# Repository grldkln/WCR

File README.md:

Please note that this repository is used only as a showcase for my final thesis project.
All of the designs are made by myself, with some code dependencies.
This project is not meant to be developed further, but can be used as a reference or as an example.

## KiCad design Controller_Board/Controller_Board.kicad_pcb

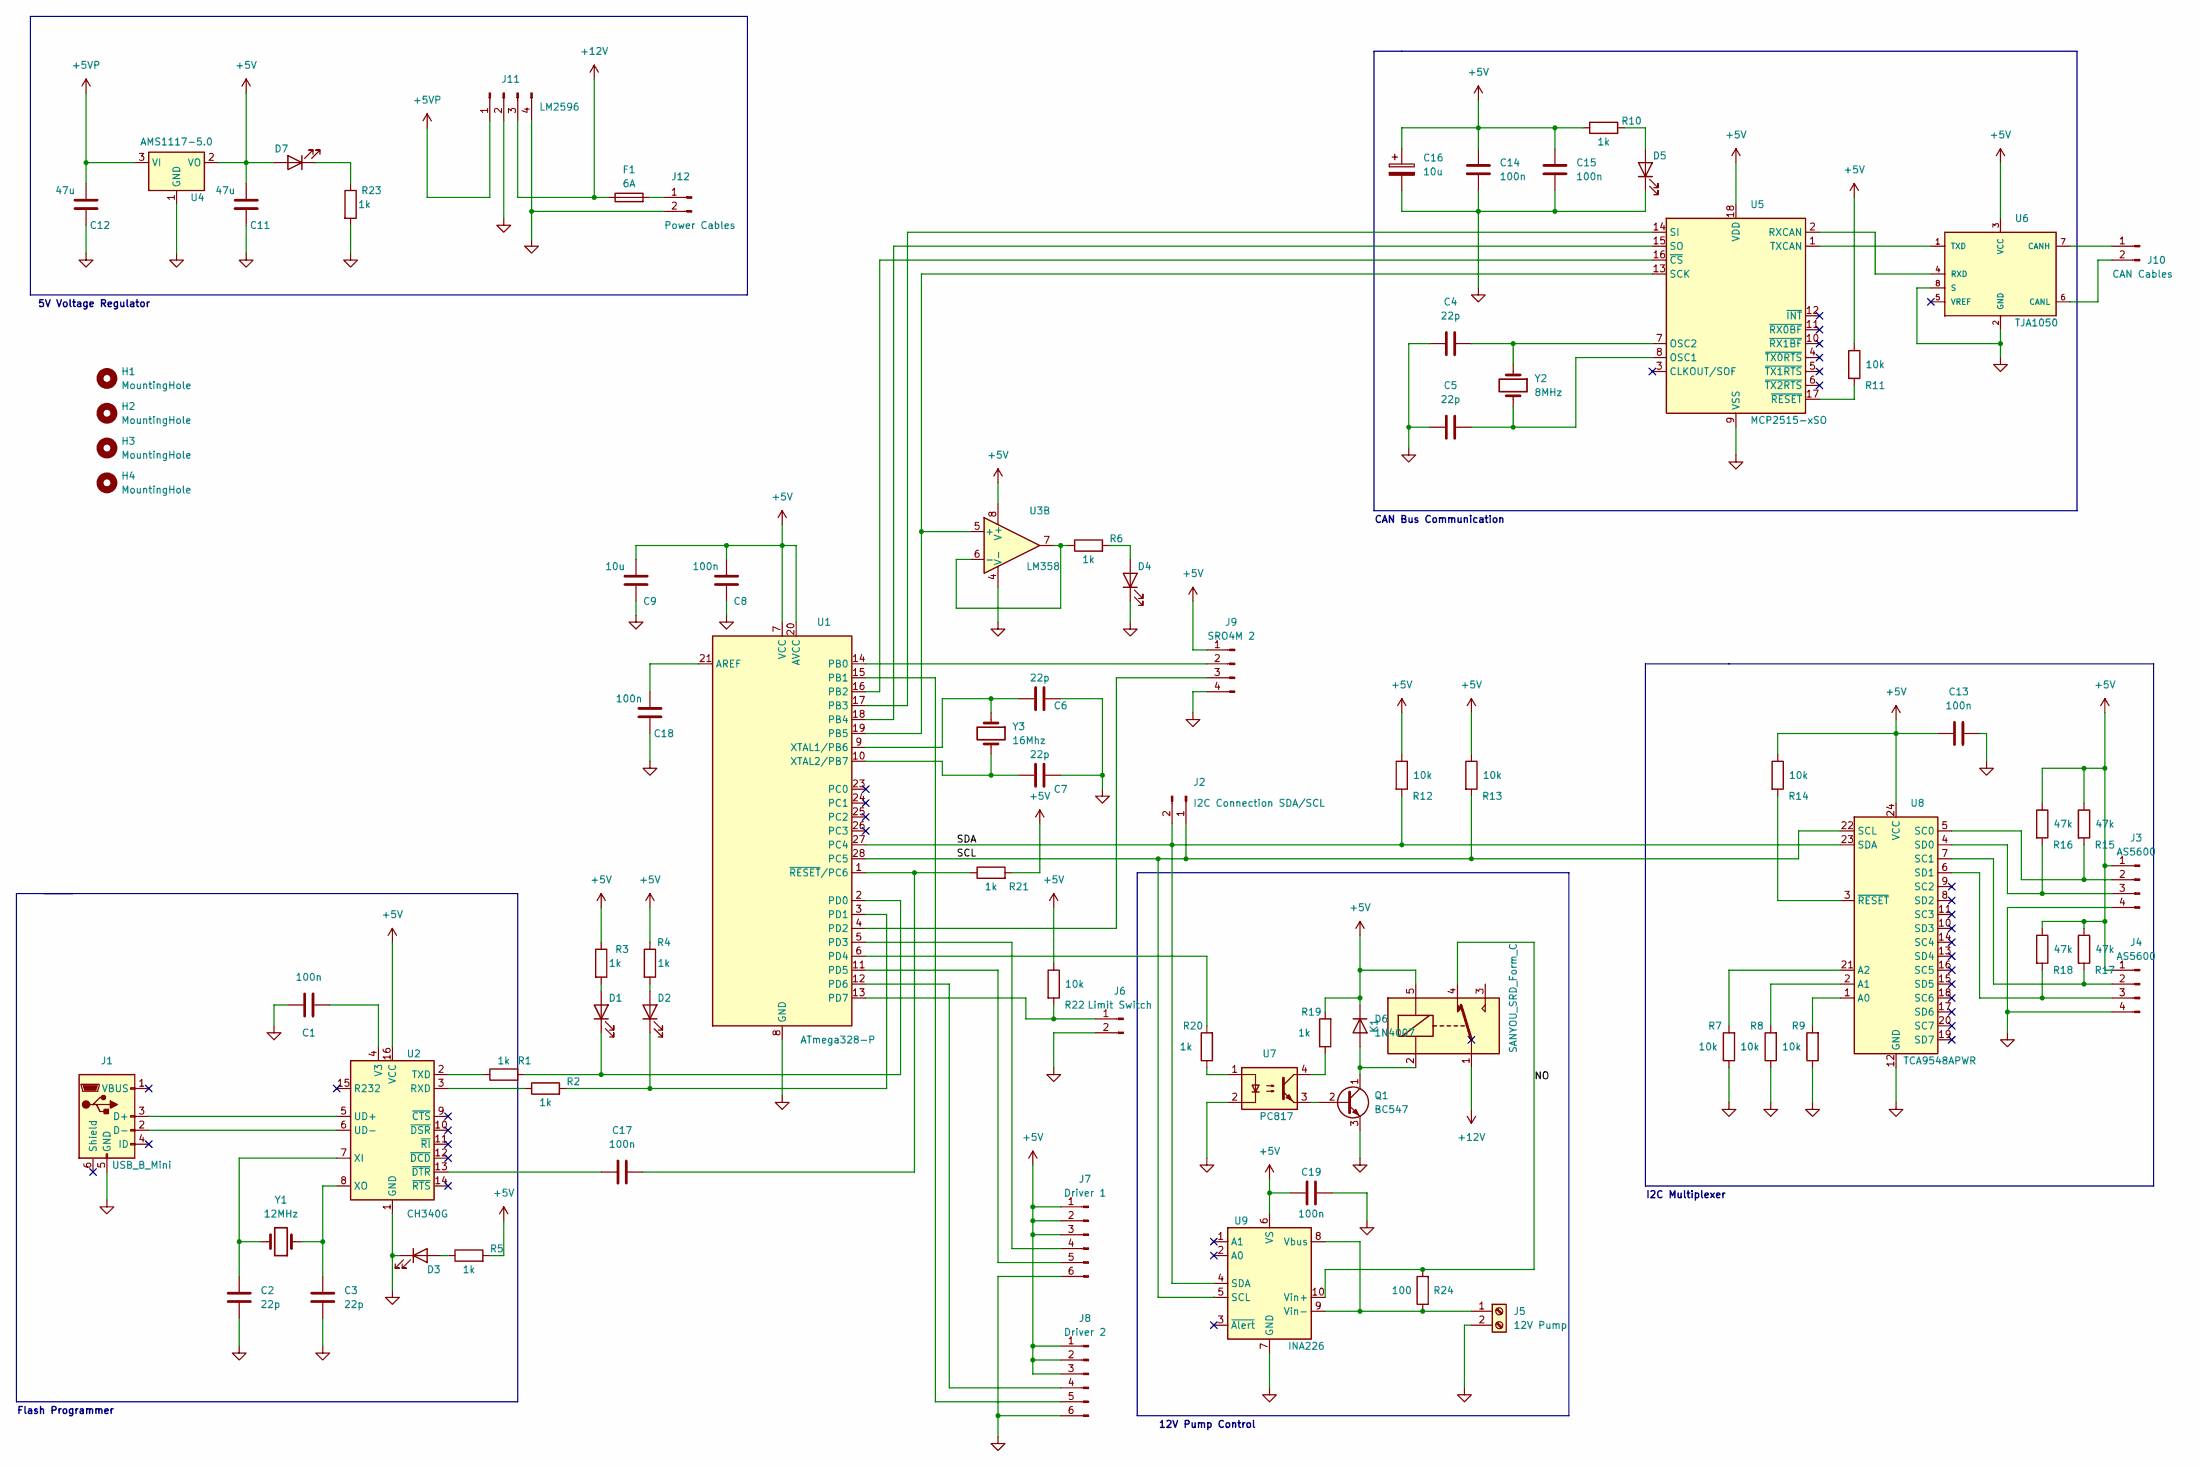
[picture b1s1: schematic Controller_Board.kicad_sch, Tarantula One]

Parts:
C1, C8, C13, C14, C15, C17, C18, C19: 100n; C_0805_2012Metric
C2, C3, C4, C5, C6, C7: 22p; C_0603_1608Metric
C9: 10u; C_0805_2012Metric
C11, C12: 47u; CP_Elec_8x10
C16: 10u; C_1206_3216Metric
D1, D2, D3, D4, D5, D7: LED; LED_0603_1608Metric
D6: 1N4007; D_DO-41_SOD81_P10.16mm_Horizontal
F1: 6A; Fuse_1206_3216Metric
H1, H2, H3, H4: MountingHole; MountingHole_3mm
J1: USB_B_Mini; USB_Mini-B_Lumberg_2486_01_Horizontal
J2: I2C Connection SDA/SCL; PinHeader_1x02_P2.54mm_Vertical
J3, J4: AS5600; JST_PH_B4B-PH-K_1x04_P2.00mm_Vertical
J5: 12V Pump; TerminalBlock_TE_282834-2_1x02_P2.54mm_Horizontal
J6: Limit Switch; JST_PH_B2B-PH-K_1x02_P2.00mm_Vertical
J7: Driver 1; JST_PH_B6B-PH-K_1x06_P2.00mm_Vertical
J8: Driver 2; JST_PH_B6B-PH-K_1x06_P2.00mm_Vertical
J9: SRO4M 2; JST_PH_B4B-PH-K_1x04_P2.00mm_Vertical
J10: CAN Cables; Pad_2X
J11: LM2596; TerminalBlock_TE_282834-4_1x04_P2.54mm_Horizontal
J12: Power Cables; Pad_2X
K1: SANYOU_SRD_Form_C; Relay_SPDT_SANYOU_SRD_Series_Form_C
Q1: BC547; TSOT-23
R1, R2, R3, R4, R5, R6, R10, R19, R20, R21, R23: 1k; R_0805_2012Metric
R7, R8, R9, R11, R12, R13, R14, R22: 10k; R_0805_2012Metric
R15, R16, R17, R18: 47k; R_0805_2012Metric
R24: 100; R_2512_6332Metric
U1: ATmega328-P; DIP-28_W7.62mm
U2: CH340G; SOIC-16_3.9x9.9mm_P1.27mm
U3: LM358; SOIC-8_3.9x4.9mm_P1.27mm
U4: AMS1117-5.0; SOT-223-3_TabPin2
U5: MCP2515-xSO; SOIC-18W_7.5x11.6mm_P1.27mm
U6: TJA1050; SOT96-1
U7: PC817; DIP-4_W7.62mm
U8: TCA9548APWR; TSSOP-24_4.4x7.8mm_P0.65mm
U9: INA226; VSSOP-10_3x3mm_P0.5mm
Y1: 12MHz; Crystal_HC49-U_Vertical
Y2: 8MHz; Crystal_HC49-U_Vertical
Y3: 16Mhz; Crystal_HC49-U_Vertical

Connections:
+5V: C8.2, C9.2, C11.2, C13.1, C14.1, C15.1, C16.1, C19.1, D6.1 (K), D7.2 (A), J3.1, J4.1, J7.1, J7.2, J7.3, J8.1, J8.2, J8.3, J9.1, K1.5, R3.1, R4.1, R5.2, R10.1, R11.1, R12.1, R13.1, R14.1, R15.1, R16.1, R17.1, R18.1, R19.2, R21.2, R22.1, U1.7 (VCC), U1.20 (AVCC), U2.16 (VCC), U3.8 (V+), U4.2 (VO), U5.18 (VDD), U6.3 (VCC), U8.24 (VCC), U9.6 (VS)
+5VP: C12.2, J11.1, U4.3 (VI)
+12V: F1.1, J11.3, K1.1
/NO: K1.4, R24.2, U9.10 (Vin+)
/SCL: J2.1, R13.2, U1.28 (PC5), U8.22 (SCL), U9.5 (SCL)
/SDA: J2.2, R12.2, U1.27 (PC4), U8.23 (SDA), U9.4 (SDA)
GND: C1.1, C2.2, C3.2, C4.2, C5.2, C6.1, C7.1, C8.1, C9.1, C11.1, C12.1, C13.2, C14.2, C15.2, C16.2, C18.1, C19.2, D3.1 (K), D4.1 (K), D5.1 (K), J1.5 (GND), J3.4, J4.4, J5.2, J6.2, J7.6, J8.6, J9.4, J11.2, J11.4, J12.2, Q1.3 (E), R7.1, R8.1, R9.1, R23.2, U1.8 (GND), U1.22 (GND), U2.1 (GND), U3.4 (V-), U4.1 (GND), U5.9 (VSS), U6.2 (GND), U6.8 (S), U7.2, U8.12 (GND), U9.7 (GND)
unnamed: D1.2 (A), R3.2
unnamed: D1.1 (K), R1.2, U1.2 (PD0)
unnamed: D2.2 (A), R4.2
unnamed: D2.1 (K), R2.2, U1.3 (PD1)
unnamed: D3.2 (A), R5.1
unnamed: D4.2 (A), R6.2
unnamed: D5.2 (A), R10.2
unnamed: D6.2 (A), K1.2, Q1.1 (C)
unnamed: D7.1 (K), R23.1
unnamed: J1.3 (D+), U2.5 (UD+)
unnamed: J1.2 (D-), U2.6 (UD-)
unnamed: J3.2, R15.2, U8.5 (SC0)
unnamed: J3.3, R16.2, U8.4 (SD0)
unnamed: J4.2, R17.2, U8.7 (SC1)
unnamed: J4.3, R18.2, U8.6 (SD1)
unnamed: J5.1, R24.1, U9.8 (Vbus), U9.9 (Vin-)
unnamed: J6.1, R22.2, U1.13 (PD7)
unnamed: J7.4, U1.5 (PD3)
unnamed: J7.5, U1.11 (PD5)
unnamed: J8.4, U1.12 (PD6)
unnamed: J8.5, U1.15 (PB1)
unnamed: J9.2, U1.14 (PB0)
unnamed: J9.3, U1.4 (PD2)
unnamed: J10.1, U6.7 (CANH)
unnamed: J10.2, U6.6 (CANL)
unnamed: F1.2, J12.1
unnamed: Q1.2 (B), U7.3
unnamed: R19.1, U7.4
unnamed: R20.1, U7.1
unnamed: C18.2, U1.21 (AREF)
unnamed: U1.16 (PB2), U5.16 (~CS)
unnamed: U1.17 (PB3), U5.14 (SI)
unnamed: U1.18 (PB4), U5.15 (SO)
unnamed: U1.19 (PB5), U3.5 (+), U5.13 (SCK)
unnamed: R20.2, U1.6 (PD4)
unnamed: C6.2, U1.9 (XTAL1/PB6), Y3.1
unnamed: C7.2, U1.10 (XTAL2/PB7), Y3.2
unnamed: C17.2, R21.1, U1.1 (~RESET/PC6)
unnamed: R2.1, U2.3 (RXD)
unnamed: R1.1, U2.2 (TXD)
unnamed: C1.2, U2.4 (V3)
unnamed: C2.1, U2.7 (XI), Y1.2
unnamed: C3.1, U2.8 (XO), Y1.1
unnamed: C17.1, U2.13 (~DTR)
unnamed: R6.1, U3.6 (-), U3.7
unnamed: C5.1, U5.8 (OSC1), Y2.2
unnamed: C4.1, U5.7 (OSC2), Y2.1
unnamed: U5.2 (RXCAN), U6.4 (RXD)
unnamed: U5.1 (TXCAN), U6.1 (TXD)
unnamed: R11.2, U5.17 (~RESET)
unnamed: R9.2, U8.1 (A0)
unnamed: R8.2, U8.2 (A1)
unnamed: R7.2, U8.21 (A2)
unnamed: R14.2, U8.3 (~RESET)

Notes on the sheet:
I2C Multiplexer
12V Pump Control
5V Voltage Regulator
CAN Bus Communication
Flash Programmer

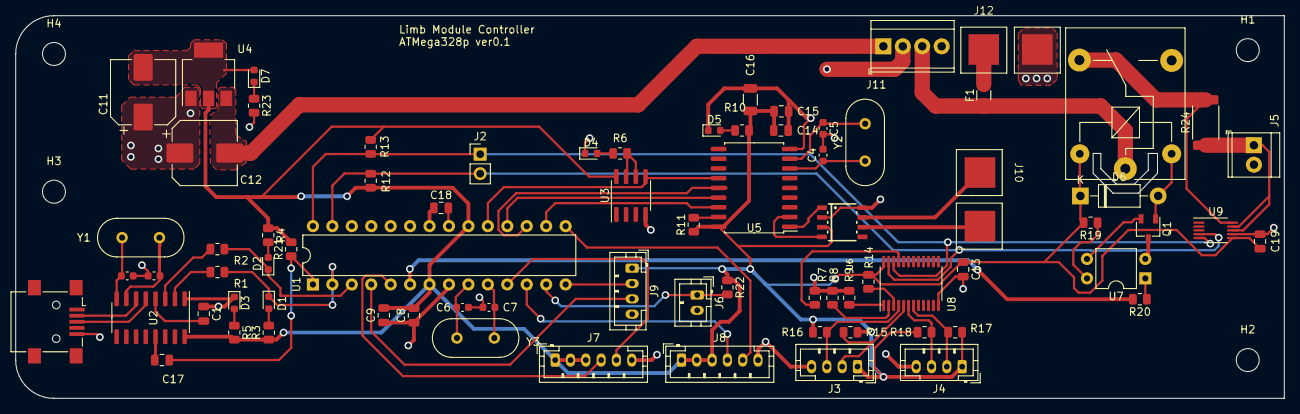
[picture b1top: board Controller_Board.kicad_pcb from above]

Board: 2 copper layers, 165.8 x 50.0 mm, 80 parts (0 on the bottom side), 61 nets.
